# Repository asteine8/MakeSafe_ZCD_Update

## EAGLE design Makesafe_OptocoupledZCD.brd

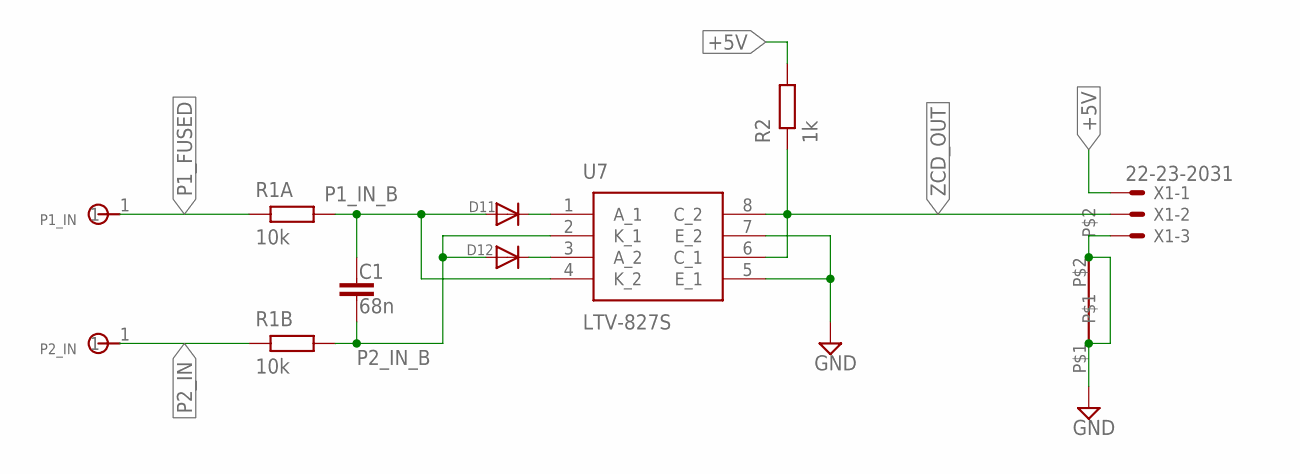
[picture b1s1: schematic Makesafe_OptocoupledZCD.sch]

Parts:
C1: 68n; 0204/7_TH
D11, D12: DIODE; 0204/7_TH
P1_IN, P2_IN: 90MIL_TERMINAL
R1A, R1B: 10k; 0204/7_TH
R2: 1k; 0204/7_TH
U7: LTV-827S; SOP254P1016X460-8N
U$1: JUMPER; 0204/7_TH
X1: 22-23-2031

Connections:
+5V: R2.P$2, X1.1
GND: U7.5 (E_1), U7.7 (E_2), U$1.P$1, U$1.P$2, X1.3
unnamed: D12.P$2 (C), U7.3 (A_2)
unnamed: D11.P$2 (C), U7.1 (A_1)
P1_FUSED: P1_IN.1, R1A.P$1
P1_IN_B: C1.P$1 (1), D11.P$1 (A), R1A.P$2, U7.4 (K_2)
P2_IN: P2_IN.1, R1B.P$1
P2_IN_B: C1.P$2 (2), D12.P$1 (A), R1B.P$2, U7.2 (K_1)
ZCD_OUT: R2.P$1, U7.6 (C_1), U7.8 (C_2), X1.2

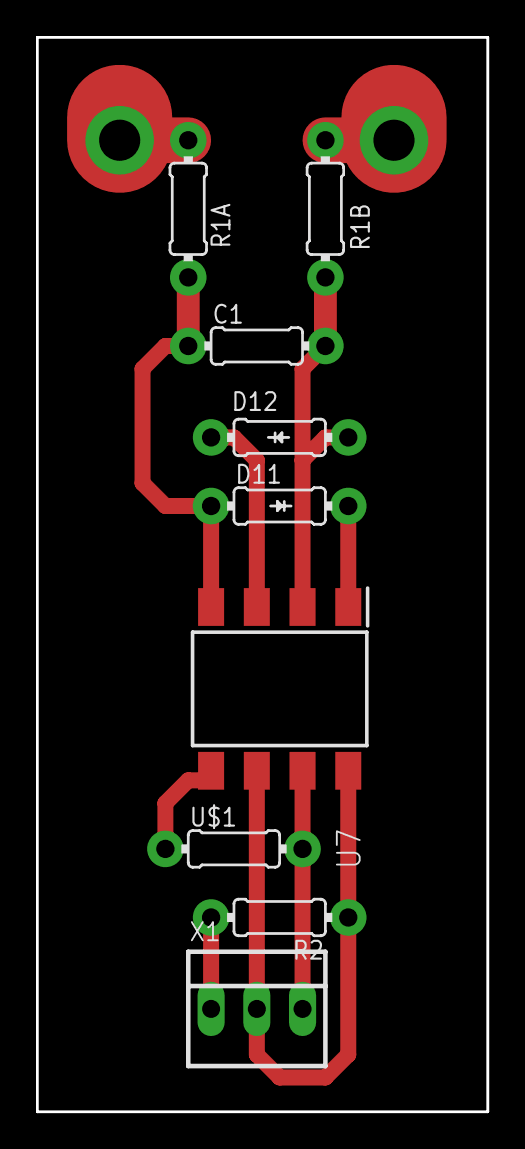
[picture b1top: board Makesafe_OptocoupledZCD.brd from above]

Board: 2 copper layers, 25.0 x 59.7 mm, 11 parts (0 on the bottom side), 9 nets.

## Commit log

2022-04-02 Exported board as gerber and exelon then created most geometry in flatcam. Still needs drills
2022-04-02 Added drills to flatcam file and exported gcode
